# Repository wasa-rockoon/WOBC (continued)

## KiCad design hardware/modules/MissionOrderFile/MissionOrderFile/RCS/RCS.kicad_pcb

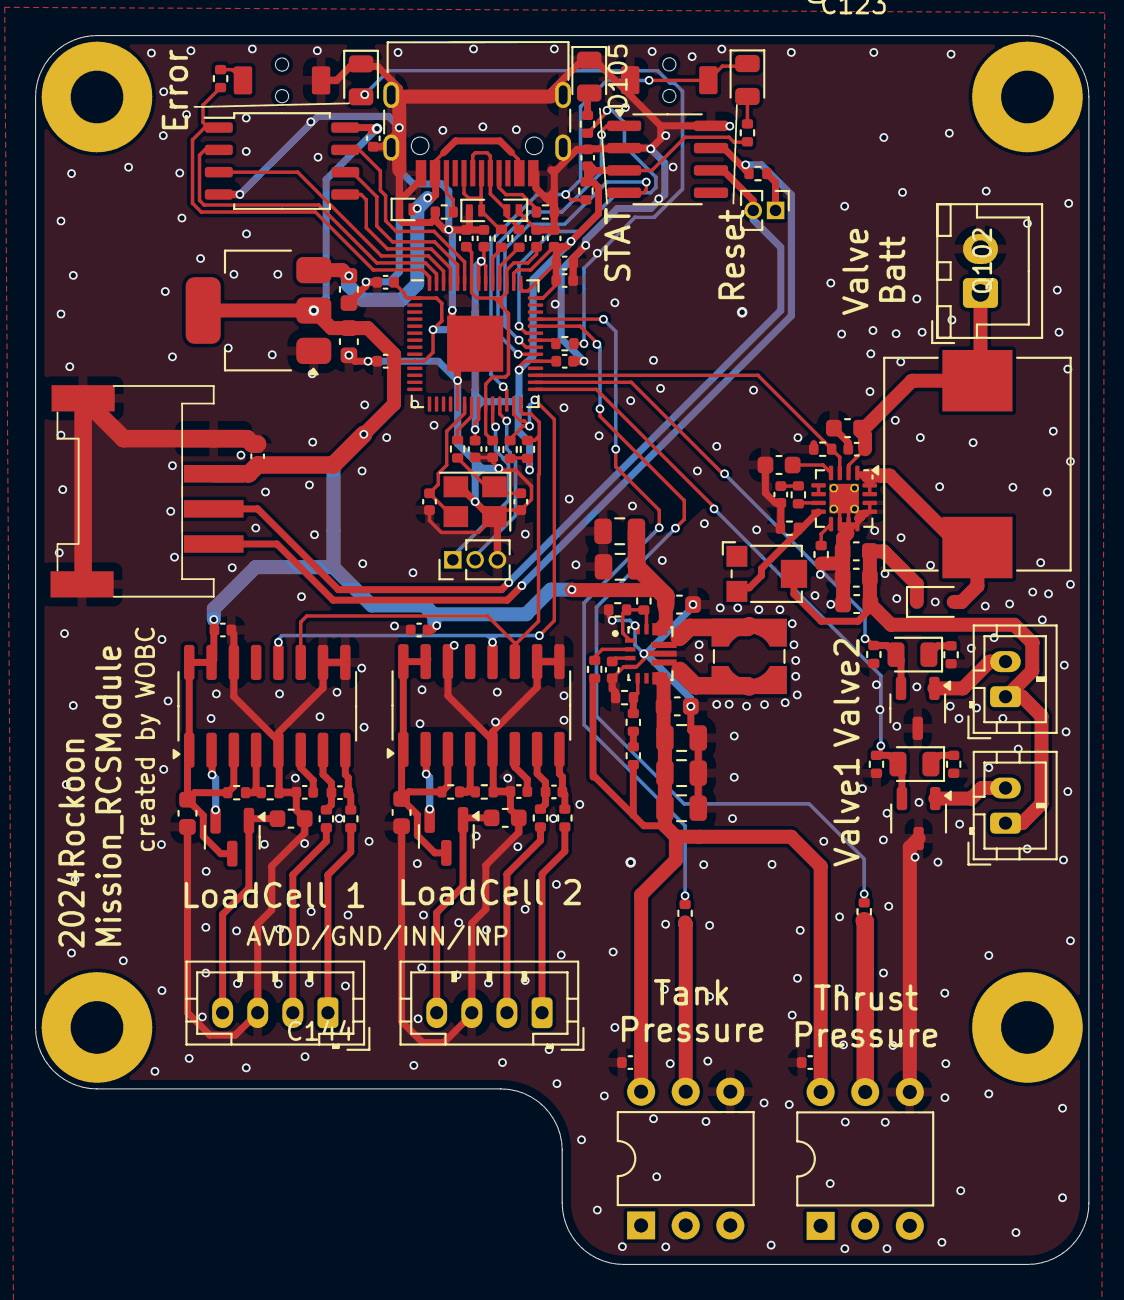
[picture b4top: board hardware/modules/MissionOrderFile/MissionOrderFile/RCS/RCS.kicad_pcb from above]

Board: 2 copper layers, 60.0 x 70.0 mm, 120 parts (0 on the bottom side), 78 nets.

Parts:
C101, C102: 10u; C_0603_1608Metric
C103, C104, C107, C108, C110, C112, C113, C114, C115, C116, C117, C118, C139, C144, C145: 100nF; C_0402_1005Metric
C105, C106: 27pF; C_0402_1005Metric
C109, C111: 1uF; C_0402_1005Metric
C119: 47nF; C_0603_1608Metric
C120, C126, C129, C131, C134, C138, C140: 10uF; C_0603_1608Metric
C121, C122, C127, C128, C130, C132, C133, C135: 0.1uF; C_0402_1005Metric
C123, C124, C125: 4.7uF; C_0603_1608Metric
C136, C137, C141, C142, C143: 22uF; C_0805_2012Metric
D101: RESET; LED_0805_2012Metric
D102, D103, D104: 5V; D_SOD-882
D105: STAT; LED_0805_2012Metric
D106: ERROR; LED_0805_2012Metric
D107: D; D_SOD-323
D108, D109: LED; D_0805_2012Metric
J101: Conn_01x02; JST_XH_B2B-XH-A_1x02_P2.50mm_Vertical
J102: DEBUG; PinHeader_1x03_P1.27mm_Vertical
J103: Jumper; PinHeader_1x02_P1.27mm_Vertical
J104: Conn_01x04_MountingPin; Grove_4P_L_SMD
J105, J106: Conn_01x02; JST_PH_B2B-PH-K_1x02_P2.00mm_Vertical
J107, J108: Conn_01x04; JST_PH_B4B-PH-K_1x04_P2.00mm_Vertical
L101: L; L_Chilisin_BMRF00101040
L102: L; L_Wuerth_WE-TPC-3816
Q101, Q102: NMOS; SOT-23-3
Q103, Q104: PNP; SOT-23
R101, R109, R111, R123, R127, R128, R131: 10k; R_0402_1005Metric
R102, R105, R108, R110, R112, R117, R132, R134, R135, R136, R137: 1k; R_0402_1005Metric
R103, R104: 5.1k; R_0402_1005Metric
R106, R107: 22.4; R_0402_1005Metric
R113: 120; R_0402_1005Metric
R114, R115, R118, R119, R130: 100k; R_0402_1005Metric
R116: 2.2k; R_0402_1005Metric
R120, R121, R124, R125: 100; R_0402_1005Metric
R122, R126: 22k; R_0402_1005Metric
R129: 330k; R_0402_1005Metric
R133: 51k; R_0402_1005Metric
RV101: 20k; Potentiometer_Bourns_TC33X_Vertical
SW101: RESET_sw; TVAF06-A020B-R
SW102: BOOT0; TVAF06-A020B-R
U101: AMS1117-3.3; SOT-223-3_TabPin2
U102: SN65HVD230; SOIC-8_3.9x4.9mm_P1.27mm
U103: W25Q128JVS; SOIC-8_5.23x5.23mm_P1.27mm
U104: RP2040; QFN-56-1EP_7x7mm_P0.4mm_EP3.2x3.2mm
U105: WQFN-16-1EP_3x3mm_P0.5mm_EP1.68x1.68mm_ThermalVias
U106, U107: HX711; SOP-16_3.9x9.9mm_P1.27mm
U108: TPS63070RNMR; VREG_TPS63070RNMR
U109, U110: DIP-6_W7.62mm
USB101: USB_C_Receptacle_USB2.0; USB_C_TYPEC-301S-ACP16X7
Y101: Crystal_GND24; Crystal_SMD_3225-4Pin_3.2x2.5mm

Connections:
/IF/CANH: J104.1, R113.2, U102.7 (CANH)
/IF/CANL: J103.2, J104.2, U102.6 (CANL)
/RCS/RCS_EN: R114.1, U104.31 (GPIO20), U105.3 (EN)
/RCS/valve1: D108.2 (A), Q101.2 (G), R118.1, U104.30 (GPIO19)
/RCS/valve2: D109.2 (A), Q102.2 (G), R119.1, U104.29 (GPIO18)
/RP2040/CAN_RX: U102.4 (R), U104.35 (GPIO23)
/RP2040/CAN_TX: U102.1 (D), U104.34 (GPIO22)
/RP2040/GPIO26_ADC0: R134.2, U104.38 (GPIO26_ADC0)
/RP2040/GPIO27_ADC1: R135.2, U104.39 (GPIO27_ADC1)
/RP2040/USB_D+: D103.2 (A2), R106.1, USB101.A6 (D+), USB101.B6 (D+)
/RP2040/USB_D-: D104.2 (A2), R107.1, USB101.A7 (D-), USB101.B7 (D-)
/SCL: R111.2, U104.28 (GPIO17), U106.11 (PD_SCK), U107.11 (PD_SCK)
/SDA: R109.2, U104.27 (GPIO16), U106.12 (DOUT), U107.12 (DOUT)
GND: C101.2, C102.2, C103.1, C104.1, C105.1, C106.1, C107.2, C108.2, C109.1, C110.2, C111.1, C112.2, C113.2, C114.2, C115.2, C116.2, C117.2, C118.1, C119.2, C120.2, C121.2, C122.2, C123.2, C124.2, C125.2, C126.2, C128.2, C129.2, C130.2, C131.2, C133.2, C134.2, C135.2, C136.2, C137.2, C138.2, C139.2, C140.2, C141.2, C142.2, C143.2, C144.2, C145.2, D102.1 (A1), D103.1 (A1), D104.1 (A1), D105.1 (K), D106.1 (K), J101.2, J102.3, J104.4, J104.MP (MountPin), J107.3, J108.3, Q101.3 (S), Q102.3 (S), R103.2, R104.2, R114.2, R115.2, R117.2, R118.2, R119.2, R123.2, R127.2, R129.2, R131.1, R136.2, R137.2, SW101.2, SW102.1, U101.1 (GND), U102.2 (GND), U102.8 (Rs), U103.4 (GND), U104.19 (TESTEN), U104.57 (GND), U105.5 (SYNC), U105.6 (AGND), U105.10 (NC), U105.11 (PGND), U105.12 (PGND), U105.13 (PGND), U105.14 (NC), U105.17 (EP), U106.5 (AGND), U106.9 (INB-), U106.10 (INB+), U106.14 (XI), U107.5 (AGND), U107.9 (INB-), U107.10 (INB+), U107.14 (XI), U108.4 (GND), U108.10 (PGND), U108.15 (VSEL), U109.6 (GND), U110.6 (GND), USB101.A1 (GND), USB101.A12 (GND), USB101.B1 (GND), USB101.B12 (GND), USB101.S1 (SHIELD), Y101.2, Y101.4
unnamed: C106.2, R108.1, Y101.1
unnamed: C121.1, R116.2
unnamed: D101.2 (A), R102.2
unnamed: D105.2 (A), R110.2
unnamed: D106.2 (A), R112.2
unnamed: D107.2 (A), L101.2, U105.1 (SW), U105.15 (SW), U105.16 (SW)
unnamed: C123.1, C124.1, C125.1, D107.1 (K), J105.1, J106.1, RV101.2
unnamed: D108.1 (K), R136.1
unnamed: D109.1 (K), R137.1
unnamed: J102.1, U104.24 (SWCLK)
unnamed: J102.2, U104.25 (SWD)
unnamed: J103.1, R113.1
unnamed: J105.2, Q101.1 (D)
unnamed: J106.2, Q102.1 (D)
unnamed: J107.1, R120.1
unnamed: J107.2, R121.1
unnamed: C126.1, J107.4, Q103.1 (C)
unnamed: J108.1, R124.1
unnamed: J108.2, R125.1
unnamed: C131.1, J108.4, Q104.1 (C)
unnamed: Q103.2 (B), U106.2 (BASE)
unnamed: Q104.2 (B), U107.2 (BASE)
unnamed: R105.2, SW102.2
unnamed: R132.2, R133.1
unnamed: U103.6 (CLK), U104.52 (QSPI_SCLK)
unnamed: U103.5 (DI(IO0)), U104.53 (QSPI_SD0)
unnamed: U103.2 (DO(IO1)), U104.55 (QSPI_SD1)
unnamed: U103.3 (IO2), U104.54 (QSPI_SD2)
unnamed: U103.7 (IO3), U104.51 (QSPI_SD3)
unnamed: R105.1, U103.1 (~CS), U104.56 (QSPI_SS)
unnamed: R112.1, U104.36 (GPIO24)
unnamed: R110.1, U104.37 (GPIO25)
unnamed: R107.2, U104.46 (USB_DM)
unnamed: R106.2, U104.47 (USB_DP)
unnamed: C107.1, C108.1, C109.2, U104.23 (DVDD), U104.45 (VREG_VOUT), U104.50 (DVDD)
unnamed: C105.2, U104.20 (XIN), Y101.3
unnamed: R108.2, U104.21 (XOUT)
unnamed: R116.1, U105.7 (COMP)
unnamed: R117.1, RV101.3, U105.8 (FB)
unnamed: R115.1, U105.9 (FREQ)
unnamed: C119.1, U105.4 (SS)
unnamed: C127.1, R120.2, U106.8 (INA+)
unnamed: C127.2, R121.2, U106.7 (INA-)
unnamed: C128.1, U106.6 (VBG)
unnamed: R122.2, R123.1, U106.4 (VFB)
unnamed: C132.1, R124.2, U107.8 (INA+)
unnamed: C132.2, R125.2, U107.7 (INA-)
unnamed: C133.1, U107.6 (VBG)
unnamed: R126.2, R127.1, U107.4 (VFB)
unnamed: R128.1, R129.1, U108.1 (PS/SYNC), U108.14 (EN)
unnamed: R131.2, R132.1, U108.5 (FB)
unnamed: L102.1, U108.11 (L1)
unnamed: L102.2, U108.9 (L2)
unnamed: R130.2, U108.2 (PG)
unnamed: C139.1, U108.3 (VAUX)
unnamed: C140.1, C141.1, C142.1, C143.1, C144.1, C145.1, R130.1, R133.2, U108.7_8 (VOUT), U109.4 (VDD), U110.4 (VDD)
unnamed: R134.1, U109.5 (VOUT)
unnamed: R135.1, U110.5 (VOUT)
unnamed: R103.1, USB101.A5 (CC1)
unnamed: R104.1, USB101.B5 (CC2)
RCS_VIN: C120.1, C122.1, J101.1, L101.1, U105.2 (VIN)
RESET: D101.1 (K), R101.2, SW101.1, U104.26 (RUN)
VBUS: C101.1, D102.2 (A2), U101.3 (VI), USB101.A4 (VBUS), USB101.A9 (VBUS), USB101.B4 (VBUS), USB101.B9 (VBUS)
VDD: C102.1, C103.2, C104.2, C110.1, C111.2, C112.1, C113.1, C114.1, C115.1, C116.1, C117.1, C118.2, C129.1, C130.1, C134.1, C135.1, C136.1, C137.1, C138.1, J104.3, Q103.3 (E), Q104.3 (E), R101.1, R102.1, R109.1, R111.1, R122.1, R126.1, R128.2, U101.2 (VO), U102.3 (VCC), U103.8 (VCC), U104.1 (IOVDD), U104.10 (IOVDD), U104.22 (IOVDD), U104.33 (IOVDD), U104.42 (IOVDD), U104.43 (ADC_AVDD), U104.44 (VREG_IN), U104.48 (USB_VDD), U104.49 (IOVDD), U106.1 (VSUP), U106.3 (AVDD), U106.15 (RATE), U106.16 (DVDD), U107.1 (VSUP), U107.3 (AVDD), U107.15 (RATE), U107.16 (DVDD), U108.12_13 (VIN)

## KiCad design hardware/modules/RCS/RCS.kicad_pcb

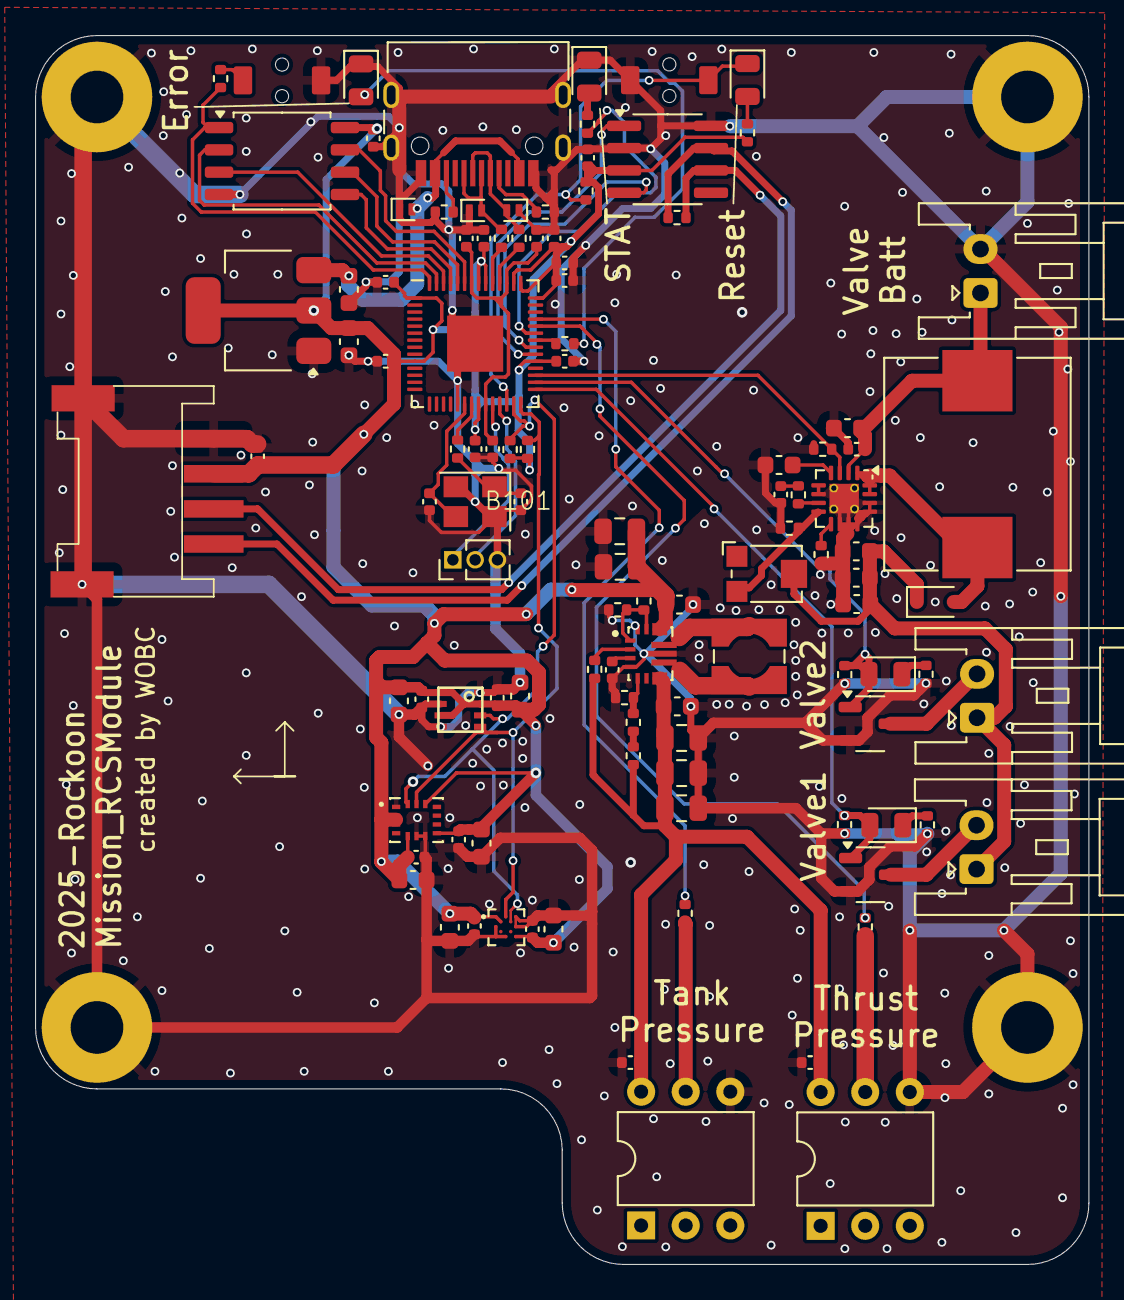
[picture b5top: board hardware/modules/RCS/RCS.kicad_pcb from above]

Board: 2 copper layers, 60.0 x 70.0 mm, 111 parts (0 on the bottom side), 61 nets.

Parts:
B101: Board_1U_60x70
C101, C102: 10u; C_0603_1608Metric
C201, C202, C205, C206, C208, C210, C211, C212, C213, C214, C215, C301, C504, C509, C510, C602, C604, C606, C608, C702, C703: 100nF; C_0402_1005Metric
C203, C204: 27pF; C_0402_1005Metric
C207, C209: 1uF; C_0402_1005Metric
C401: 47nF; C_0603_1608Metric
C402, C503, C505, C601, C603, C605, C607: 10uF; C_0603_1608Metric
C403, C404: 0.1uF; C_0402_1005Metric
C405, C406, C407: 4.7uF; C_0603_1608Metric
C501, C502, C506, C507, C508: 22uF; C_0805_2012Metric
C701, C704: 10μF; C_0603_1608Metric
D201: RESET; LED_0805_2012Metric
D202, D203, D204: 5V; D_SOD-882
D205: STAT; LED_0805_2012Metric
D206: ERROR; LED_0805_2012Metric
D401: D; D_SOD-323
D402, D403: LED; D_0805_2012Metric
J101, J401, J402: Conn_01x02; JST_XA_S02B-XASK-1N-BN_1x02_P2.50mm_Horizontal
J201: DEBUG; PinHeader_1x03_P1.27mm_Vertical
J301: Conn_01x04_MountingPin; Grove_4P_L_SMD
L401: L; L_Chilisin_BMRF00101040
L501: L; L_Wuerth_WE-TPC-3816
Q401, Q402: Q_NMOS_GSD; SOT-23-3
R201, R209, R211, R501, R504: 10k; R_0402_1005Metric
R202, R205, R208, R210, R212, R404, R405, R407, R505, R507, R508: 1k; R_0402_1005Metric
R203, R204: 5.1k; R_0402_1005Metric
R206, R207: 22.4; R_0402_1005Metric
R301: 120; R_0402_1005Metric
R401, R402, R406, R408, R503: 100k; R_0402_1005Metric
R403: 2.2k; R_0402_1005Metric
R502: 330k; R_0402_1005Metric
R506: 51k; R_0402_1005Metric
RV401: 20k; Potentiometer_Bourns_TC33X_Vertical
SW201: RESET_sw; TVAF06-A020B-R
SW202: BOOT0; TVAF06-A020B-R
U101: AMS1117-3.3; SOT-223-3_TabPin2
U201: SN65HVD230; SOIC-8_3.9x4.9mm_P1.27mm
U202: W25Q128JVS; SOIC-8_5.3x5.3mm_P1.27mm
U203: RP2040; QFN-56-1EP_7x7mm_P0.4mm_EP3.2x3.2mm
U401: WQFN-16-1EP_3x3mm_P0.5mm_EP1.68x1.68mm_ThermalVias
U501: TPS63070RNMR; VREG_TPS63070RNMR
U502, U503: DIP-6_W7.62mm
U601: BMM150; XDCR_BMM150
U602: BMI270; XDCR_BMI270
U701: BME280
USB201: USB_C_Receptacle_USB2.0; USB_C_TYPEC-301S-ACP16X7
Y201: Crystal_GND24; Crystal_SMD_3225-4Pin_3.2x2.5mm

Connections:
/IF/CANH: J301.1, R301.2, U201.7 (CANH)
/IF/CANL: J301.2, R301.1, U201.6 (CANL)
/RCS/RCS_EN: R401.1, U203.31 (GPIO20), U401.3 (EN)
/RCS/valve1: D402.2 (A), Q401.1 (G), R406.1, U203.30 (GPIO19)
/RCS/valve2: D403.2 (A), Q402.1 (G), R408.1, U203.29 (GPIO18)
/RP2040/CAN_RX: U201.4 (R), U203.35 (GPIO23)
/RP2040/CAN_TX: U201.1 (D), U203.34 (GPIO22)
/RP2040/GPIO26_ADC0: R507.2, U203.38 (GPIO26_ADC0)
/RP2040/GPIO27_ADC1: R508.2, U203.39 (GPIO27_ADC1)
/RP2040/USB_D+: D203.2 (A2), R206.1, USB201.A6 (D+), USB201.B6 (D+)
/RP2040/USB_D-: D204.2 (A2), R207.1, USB201.A7 (D-), USB201.B7 (D-)
/SCL: R211.2, U203.28 (GPIO17), U601.A3 (SCK), U602.13 (SCX), U701.4 (SCK)
/SDA: R209.2, U203.27 (GPIO16), U601.B4 (SDI), U602.14 (SDX), U701.3 (SDI)
GND: B101.GND, C101.2, C102.2, C201.1, C202.1, C203.1, C204.1, C205.2, C206.2, C207.1, C208.2, C209.1, C210.2, C211.2, C212.2, C213.2, C214.2, C215.2, C301.1, C401.2, C402.2, C403.2, C404.2, C405.2, C406.2, C407.2, C501.2, C502.2, C503.2, C504.2, C505.2, C506.2, C507.2, C508.2, C509.2, C510.2, C601.2, C602.2, C603.2, C604.2, C605.2, C606.2, C607.2, C608.2, C701.2, C702.2, C703.2, C704.2, D202.1 (A1), D203.1 (A1), D204.1 (A1), D205.1 (K), D206.1 (K), J101.2, J201.3, J301.4, J301.MP (MountPin), Q401.2 (S), Q402.2 (S), R203.2, R204.2, R401.2, R402.2, R404.2, R405.2, R406.2, R407.2, R408.2, R502.2, R504.1, SW201.2, SW202.1, U101.1 (GND), U201.2 (GND), U201.8 (Rs), U202.4 (GND), U203.19 (TESTEN), U203.57 (GND), U401.5 (SYNC), U401.6 (AGND), U401.10 (NC), U401.11 (PGND), U401.12 (PGND), U401.13 (PGND), U401.14 (NC), U401.17 (EP), U501.4 (GND), U501.10 (PGND), U501.15 (VSEL), U502.6 (GND), U503.6 (GND), U601.A5 (CSB), U601.C1 (SDO), U601.C5 (GND), U601.E1 (GND__1), U601.E3 (GND__2), U602.1 (SDO), U602.6 (GNDIO), U602.7 (GND), U701.1 (GND), U701.5 (SDO), U701.7 (GND), USB201.A1 (GND), USB201.A12 (GND), USB201.B1 (GND), USB201.B12 (GND), USB201.S1 (SHIELD), Y201.2, Y201.4
unnamed: C204.2, R208.1, Y201.1
unnamed: C403.1, R403.2
unnamed: D201.2 (A), R202.2
unnamed: D205.2 (A), R210.2
unnamed: D206.2 (A), R212.2
unnamed: D401.2 (A), L401.2, U401.1 (SW), U401.15 (SW), U401.16 (SW)
unnamed: C405.1, C406.1, C407.1, D401.1 (K), J401.1, J402.1, RV401.2
unnamed: D402.1 (K), R404.1
unnamed: D403.1 (K), R407.1
unnamed: J201.1, U203.24 (SWCLK)
unnamed: J201.2, U203.25 (SWD)
unnamed: J401.2, Q401.3 (D)
unnamed: J402.2, Q402.3 (D)
unnamed: R205.2, SW202.2
unnamed: R505.2, R506.1
unnamed: U202.6 (CLK), U203.52 (QSPI_SCLK)
unnamed: U202.5 (DI(IO0)), U203.53 (QSPI_SD0)
unnamed: U202.2 (DO(IO1)), U203.55 (QSPI_SD1)
unnamed: U202.3 (IO2), U203.54 (QSPI_SD2)
unnamed: U202.7 (IO3), U203.51 (QSPI_SD3)
unnamed: R205.1, U202.1 (~CS), U203.56 (QSPI_SS)
unnamed: R212.1, U203.36 (GPIO24)
unnamed: R210.1, U203.37 (GPIO25)
unnamed: R207.2, U203.46 (USB_DM)
unnamed: R206.2, U203.47 (USB_DP)
unnamed: C205.1, C206.1, C207.2, U203.23 (DVDD), U203.45 (VREG_VOUT), U203.50 (DVDD)
unnamed: C203.2, U203.20 (XIN), Y201.3
unnamed: R208.2, U203.21 (XOUT)
unnamed: R403.1, U401.7 (COMP)
unnamed: R405.1, RV401.3, U401.8 (FB)
unnamed: R402.1, U401.9 (FREQ)
unnamed: C401.1, U401.4 (SS)
unnamed: R501.1, R502.1, U501.1 (PS/SYNC), U501.14 (EN)
unnamed: R504.2, R505.1, U501.5 (FB)
unnamed: L501.1, U501.11 (L1)
unnamed: L501.2, U501.9 (L2)
unnamed: R503.2, U501.2 (PG)
unnamed: C504.1, U501.3 (VAUX)
unnamed: C505.1, C506.1, C507.1, C508.1, C509.1, C510.1, R503.1, R506.2, U501.7_8 (VOUT), U502.4 (VDD), U503.4 (VDD)
unnamed: R507.1, U502.5 (VOUT)
unnamed: R508.1, U503.5 (VOUT)
unnamed: R203.1, USB201.A5 (CC1)
unnamed: R204.1, USB201.B5 (CC2)
RCS_VIN: C402.1, C404.1, J101.1, L401.1, U401.2 (VIN)
RESET: D201.1 (K), R201.2, SW201.1, U203.26 (RUN)
VBUS: C101.1, D202.2 (A2), U101.3 (VI), USB201.A4 (VBUS), USB201.A9 (VBUS), USB201.B4 (VBUS), USB201.B9 (VBUS)
VDD: C102.1, C201.2, C202.2, C208.1, C209.2, C210.1, C211.1, C212.1, C213.1, C214.1, C215.1, C301.2, C501.1, C502.1, C503.1, C601.1, C602.1, C603.1, C604.1, C605.1, C606.1, C607.1, C608.1, C701.1, C702.1, C703.1, C704.1, J301.3, R201.1, R202.1, R209.1, R211.1, R501.2, U101.2 (VO), U201.3 (VCC), U202.8 (VCC), U203.1 (IOVDD), U203.10 (IOVDD), U203.22 (IOVDD), U203.33 (IOVDD), U203.42 (IOVDD), U203.43 (ADC_AVDD), U203.44 (VREG_IN), U203.48 (USB_VDD), U203.49 (IOVDD), U501.12_13 (VIN), U601.A1 (PS), U601.B2 (VDDIO), U601.E5 (VDD), U602.2 (ASDX), U602.3 (ASCX), U602.5 (VDDIO), U602.8 (VDD), U602.12 (CSB), U701.2 (CSB), U701.6 (VDDIO), U701.8 (VDD)

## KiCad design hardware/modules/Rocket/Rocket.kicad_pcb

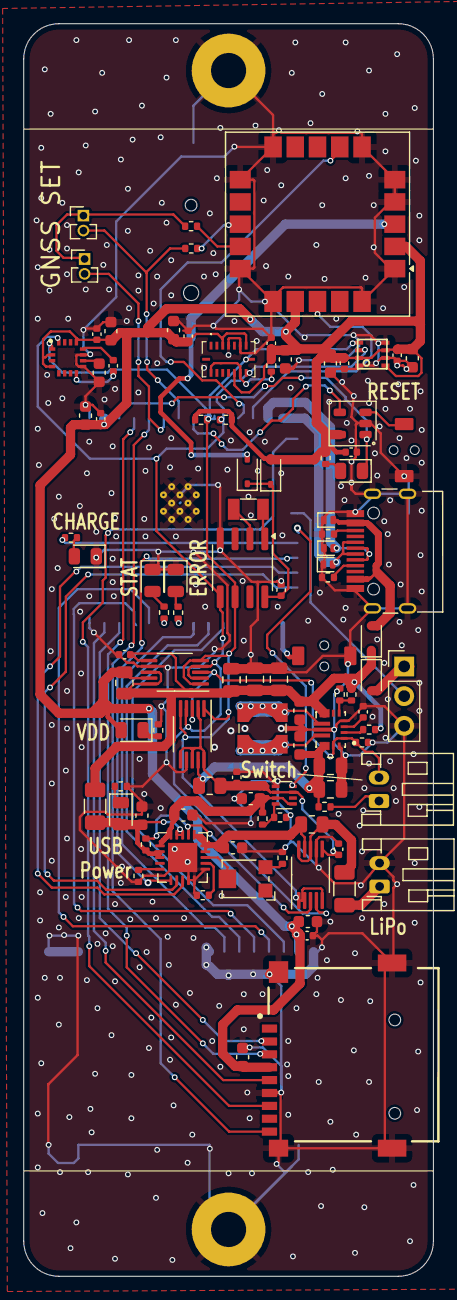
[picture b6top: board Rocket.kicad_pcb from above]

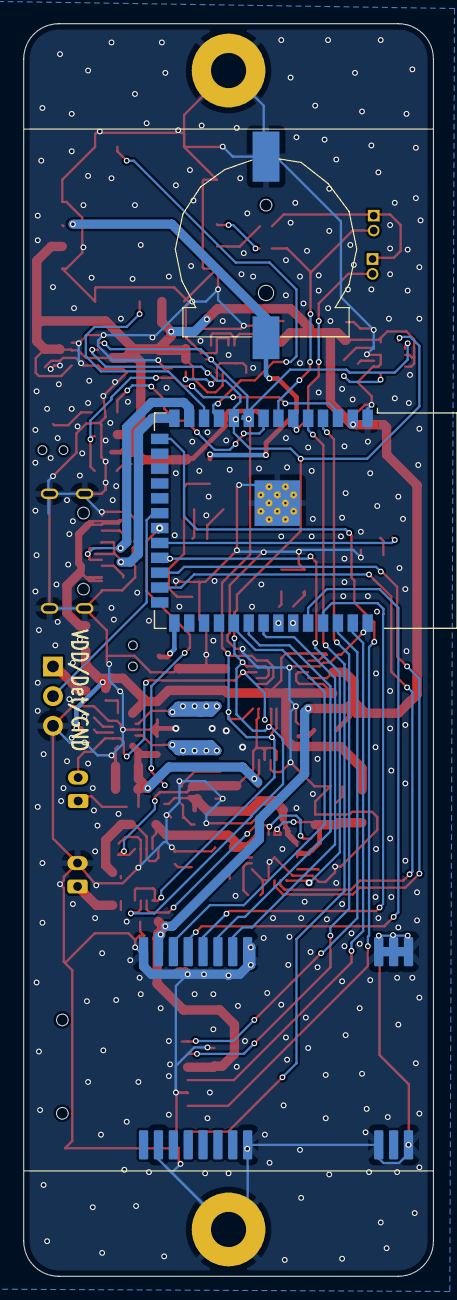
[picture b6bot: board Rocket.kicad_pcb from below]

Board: 2 copper layers, 35.0 x 107.0 mm, 103 parts (3 on the bottom side), 74 nets.

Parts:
BT101: Battery_Cell; cr1220
C101, C103, C106, C112, C113, C118, C120, C123, C125, C126, C128, C129, C134: 100nF; C_0402_1005Metric
C102, C104, C105, C109, C110, C111, C114, C119, C122, C124, C127, C130, C131, C135: 10uF; C_0603_1608Metric
C107, C108, C115, C116, C117: 22uF; C_0805_2012Metric
C132: 0.22uF; C_0402_1005Metric
C133: 4.7uF; C_0603_1608Metric
D101, D102, D103: 5V; D_SOD-882D
D104: RESET; LED_0805_2012Metric
D105: ERROR; LED_0805_2012Metric
D106: STAT; LED_0805_2012Metric
D201, D301, D401, D402: D; D_SOD-323
F101, F102: Polyfuse; Fuse_1206_3216Metric
J101: Conn_01x03; PinHeader_1x03_P2.54mm_Vertical
J102: Ext Switch; JST_PH_S2B-PH-K_1x02_P2.00mm_Horizontal
J103: LiPo; JST_PH_S2B-PH-K_1x02_P2.00mm_Horizontal
J104, J501: Conn_01x02; PinHeader_1x02_P1.27mm_Vertical
L101: L; L_Wuerth_WE-TPC-3816
LED101: USB Power; LED_0805_2012Metric
LED102: CHARGE; LED_0805_2012Metric
LED103: VDD; LED_0805_2012Metric
MICRO_SD101: TF-01A
R101, R102: 5.1k; R_0402_1005Metric
R103, R104, R106, R125, R126: 470; R_0402_1005Metric
R105, R107, R112, R113, R117: 10k; R_0402_1005Metric
R108, R109, R111, R124: 1k; R_0402_1005Metric
R110: 4.7k; R_0402_1005Metric
R114, R115, R120: 100k; R_0402_1005Metric
R116, R119, R123: 50mΩ; R_0805_2012Metric
R118: 330k; R_0402_1005Metric
R121: 15k; R_0402_1005Metric
R122: 47k; R_0402_1005Metric
R127: 4.7K; R_0402_1005Metric
RV101: 10k; Potentiometer_Bourns_TC33X_Vertical
SW101: RESET_sw; TVAF06-A020B-R
SW201: Boot_sw; TVAF06-A020B-R
U101: TPS3820; SOT-23-5
U102: ESP32-S3-WROOM-1
U103: TPS2116DRL; SOT-583-8
U104: MCP73871-1CC; QFN-20-1EP_4x4mm_P0.5mm_EP2.5x2.5mm
U105, U106, U108: INA226; VSSOP-10_3x3mm_P0.5mm
U107: TPS63070RNMR; VREG_TPS63070RNMR
U109: PCF8563T; SOIC-8_3.9x4.9mm_P1.27mm
U110: SAM-M10Q; ublox_SAM-M8Q
U111: E220-900T22S(JP)
U112: BME280
U113: BMI088
U114: QMC5883L; _HMC5883L
USB101: USB_C_Receptacle_USB2.0; USB_C_TYPEC-301S-ACP16X7
Y101: Crystal; Crystal_SMD_3215-2Pin_3.2x1.5mm

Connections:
+BATT: BT101.1 (+), D401.2 (A), U110.3 (V_BCKP)
/AUX: U102.31 (GPIO38/FSPIWP/SUBSPIWP), U111.9 (AUX)
/CHARGE: R109.2, U102.22 (GPIO14/TOUCH14/ADC2_CH3/FSPIWP/FSPIDQS/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)
/CLK: MICRO_SD101.5 (CLK), U102.39 (GPIO1/TOUCH1/ADC1_CH0)
/DetL: J101.2, U102.20 (GPIO12/TOUCH12/ADC2_CH1/FSPICLK/FSPIIO6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)
/ESP32Core2/USB_D+: D102.2 (A2), U102.14 (GPIO20/U1CTS/ADC2_CH9/CLK_OUT1/USB_D+), USB101.A6 (D+), USB101.B6 (D+)
/ESP32Core2/USB_D-: D103.2 (A2), U102.13 (GPIO19/U1RTS/ADC2_CH8/CLK_OUT2/USB_D-), USB101.A7 (D-), USB101.B7 (D-)
/ESP32Core2/WDI: U101.4 (WDI), U102.8 (GPIO15/U0RTS/ADC2_CH4/XTAL_32K_P)
/GPS_RESET: U102.12 (GPIO8/TOUCH8/ADC1_CH7/SUBSPICS1), U110.18 (~RESET)
/I2C_SCL: R105.2, U102.9 (GPIO16/U0CTS/ADC2_CH5/XTAL_32K_N), U105.1 (A1), U105.5 (SCL), U106.1 (A1), U106.2 (A0), U106.5 (SCL), U108.1 (A1), U108.5 (SCL), U109.6 (SCL), U112.4 (SCK), U113.8 (SCL/SCK), U114.1 (SCL)
/I2C_SDA: R107.2, U102.10 (GPIO17/U1TXD/ADC2_CH6), U105.4 (SDA), U106.4 (SDA), U108.2 (A0), U108.4 (SDA), U109.5 (SDA), U112.3 (SDI), U113.9 (SDA/SDI), U114.16 (SDA)
/LiPoPower2/PROG: RV101.2, U104.13 (PROG1)
/M0: U102.33 (MTDO/GPIO40/CLK_OUT2), U111.5 (M0)
/M1: U102.32 (MTCK/GPIO39/CLK_OUT3/SUBSPICS1), U111.6 (M1)
/MISO: MICRO_SD101.7 (DAT0), U102.15 (GPIO3/TOUCH3/ADC1_CH2)
/MOSI: MICRO_SD101.3 (CMD), U102.4 (GPIO4/TOUCH4/ADC1_CH3)
/PG: U102.23 (GPIO21), U104.6 (~PG)
/RTX0: U102.36 (U0RXD/GPIO44/CLK_OUT2), U111.8 (TXD)
/RTX1: J104.2, R126.2, U102.7 (GPIO7/TOUCH7/ADC1_CH6)
/SD_DET: MICRO_SD101.CD1 (CD), U102.5 (GPIO5/TOUCH5/ADC1_CH4)
/SS: MICRO_SD101.2 (CD/DAT3), U102.38 (GPIO2/TOUCH2/ADC1_CH1)
/ST: U102.21 (GPIO13/TOUCH13/ADC2_CH2/FSPIQ/FSPIIO7/S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), U103.8 (ST)
/STAT1: U102.24 (GPIO47/SPICLK_P/SUBSPICLK_P_DIFF), U104.8 (STAT1/~LBO)
/STAT2: U102.25 (GPIO48/SPICLK_N/SUBSPICLK_N_DIFF), U104.7 (STAT2)
/TRX0: U102.37 (U0TXD/GPIO43/CLK_OUT1), U111.7 (RXD)
/TRX1: J501.2, U102.6 (GPIO6/TOUCH6/ADC1_CH5)
/TimePulse: U102.11 (GPIO18/U1RXD/ADC2_CH7/CLK_OUT3), U110.7 (TIMEPULSE)
GND: BT101.2 (-), C101.1, C102.1, C103.2, C104.2, C105.2, C106.2, C107.2, C108.2, C109.2, C110.2, C111.2, C112.2, C113.2, C114.2, C115.2, C116.2, C117.2, C118.2, C119.2, C120.1, C122.2, C123.2, C124.2, C125.2, C126.2, C127.2, C128.2, C129.2, C130.2, C131.2, C133.2, C134.2, C135.2, D101.1 (A1), D102.1 (A1), D103.1 (A1), D105.1 (K), D106.1 (K), J101.3, J103.2, LED102.1 (K), MICRO_SD101.6 (VSS), MICRO_SD101.MP1 (SHIELD), MICRO_SD101.MP2 (SHIELD), MICRO_SD101.MP3 (SHIELD), MICRO_SD101.MP4 (SHIELD), R101.2, R102.2, R108.2, R110.1, R111.2, R113.2, R114.2, R118.2, R121.1, R124.2, SW101.2, SW201.2, U101.2 (GND), U102.1 (GND), U102.40 (GND), U102.41 (GND), U103.1 (GND), U104.9 (~TE), U104.10 (V_{SS}), U104.11 (V_{SS}), U104.21 (V_{SS}), U105.7 (GND), U106.7 (GND), U107.4 (GND), U107.10 (PGND), U107.15 (VSEL), U108.7 (GND), U109.4 (VSS), U110.1 (GND), U110.4 (GND), U110.5 (GND), U110.6 (GND), U110.10 (GND), U110.11 (GND), U110.15 (GND), U110.16 (GND), U110.20 (GND), U111.1 (GND), U111.2 (GND), U111.3 (GND), U111.4 (GND), U111.11 (GND), U111.13 (GND), U111.19 (GND), U111.20 (GND), U111.22 (GND), U112.1 (GND), U112.5 (SDO), U112.7 (GND), U113.4 (GNDA), U113.6 (GNDIO), U114.9 (GND), U114.11 (GND), USB101.A1 (GND), USB101.A12 (GND), USB101.B1 (GND), USB101.B12 (GND), USB101.S1 (SHIELD)
unnamed: D101.2 (A2), D201.2 (A), USB101.A4 (VBUS), USB101.A9 (VBUS), USB101.B4 (VBUS), USB101.B9 (VBUS)
unnamed: D104.2 (A), R103.2
unnamed: D105.2 (A), R104.2
unnamed: D106.2 (A), R106.2
unnamed: D301.2 (A), J101.1
unnamed: C120.2, D401.1 (K), D402.1 (K), U109.8 (VDD)
unnamed: J102.1, R117.1
unnamed: J102.2, R118.1, U105.3 (~Alert), U107.1 (PS/SYNC), U107.14 (EN), U108.3 (~Alert)
unnamed: F102.2, J103.1
unnamed: J104.1, J501.1, R125.2
unnamed: C104.1, F101.2, LED101.2 (A), R115.1, U104.2 (VPCC), U104.3 (SEL), U104.18 (IN), U104.19 (IN)
unnamed: LED101.1 (K), R108.1
unnamed: LED102.2 (A), R109.1
unnamed: LED103.1 (K), R124.1
unnamed: R111.1, RV101.3
unnamed: SW101.1, U101.3 (MR)
unnamed: SW201.1, U102.27 (GPIO0/BOOT)
unnamed: R104.1, U102.34 (MTDI/GPIO41/CLK_OUT1)
unnamed: R106.1, U102.35 (MTMS/GPIO42)
unnamed: C105.1, C109.1, R112.1, U103.3 (VIN1), U103.5 (MODE), U104.1 (OUT), U104.20 (OUT)
unnamed: R110.2, R112.2, U103.4 (PR1)
unnamed: R115.2, U104.17 (CE), U106.3 (~Alert)
unnamed: R114.1, U104.12 (PROG3)
unnamed: R113.1, U104.5 (THERM)
unnamed: C110.1, R119.1, U104.14 (V_{BAT}), U104.15 (V_{BAT}), U104.16 (V_{BAT_SENSE}), U106.9 (Vin-)
unnamed: C107.1, C108.1, C111.1, R116.2, R117.2, U105.9 (Vin-), U107.12_13 (VIN)
unnamed: F102.1, R119.2, U106.8 (Vbus), U106.10 (Vin+)
unnamed: R121.2, R122.1, U107.5 (FB)
unnamed: L101.1, U107.11 (L1)
unnamed: L101.2, U107.9 (L2)
unnamed: R120.2, U107.2 (PG)
unnamed: C113.1, U107.3 (VAUX)
unnamed: U109.1 (OSCI), Y101.1
unnamed: U109.2 (OSCO), Y101.2
unnamed: R125.1, U110.14 (RXD)
unnamed: R126.1, U110.13 (TXD)
unnamed: R127.1, U113.10 (SDO2), U113.15 (SDO1)
unnamed: C133.1, U114.10 (C1)
unnamed: C132.1, U114.12 (SETC)
unnamed: C132.2, U114.8 (STEP)
unnamed: R101.1, USB101.A5 (CC1)
unnamed: R102.1, USB101.B5 (CC2)
RESET: D104.1 (K), U101.1 (RESET), U102.3 (EN)
VBUS: C114.1, C115.1, C116.1, C117.1, C118.1, D201.1 (K), D301.1 (K), F101.1, R120.1, R122.2, R123.1, U107.7_8 (VOUT), U108.6 (VS), U108.8 (Vbus), U108.10 (Vin+)
VDD: C101.2, C102.2, C103.1, C119.1, C122.1, C123.1, C124.1, C125.1, C126.1, C127.1, C128.1, C129.1, C130.1, C131.1, C134.1, C135.1, D402.2 (A), LED103.2 (A), MICRO_SD101.4 (VDD), R103.1, R105.1, R107.1, R123.2, R127.2, U101.5 (VDD), U102.2 (3V3), U108.9 (Vin-), U110.2 (VCC_IO), U110.17 (VCC), U111.10 (VDD), U112.2 (CSB), U112.6 (VDDIO), U112.8 (VDD), U113.3 (VDD), U113.7 (PS), U113.11 (VDDIO), U114.2 (VDD), U114.4 (S1), U114.13 (VDDIO)
VPP: C106.1, C112.1, R116.1, U103.2 (VOUT), U103.7 (VOUT), U105.2 (A0), U105.6 (VS), U105.8 (Vbus), U105.10 (Vin+), U106.6 (VS)
